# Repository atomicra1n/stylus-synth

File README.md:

# Stylus Synthesizer

A small synthesizer played with a stylus or a probe (such as a multimeter one). It has 20 copper pads on the PCB acting as a keyboard, a speaker and a headphone jack. Controlled by an RP2040-Zero featuring an analog vactrol circuit.

## Features

- 20 note keyboard (note C to G) from exposed copper pads, playable with a conductive stylus
- Notes fade out naturally when the stylus is lifted (thanks to the Vactrol circuit, LED + photoresistor)
- Volume and decay knobs
- Octave button and waveform button (supports square wave, saw wave and triangle wave)
- Speaker and a headphone jack that automatically turns the speaker off when headphones are plugged in
- Can also act as a USB MIDI controller
- Fully through-hole, easy to solder

## Motivation

Week 3 of Hack Club's Half Life was all about music. I remembered an interesting musical instrument from the 60s, which had small metal pads that would play notes when touched with a stylus (the Stylophone), so I decided to make my own smaller version. I also added a small vactrol circuit to make it sound more natural instead of notes cutting off.

## Functionality

- The keyboard has a chain of 21 1 kiloohm resistors between ground and 3.3 volts. Each pad is between two resistors, so it has a different voltage than the rest. The stylus goes into an ADC pin of the RP2040, so it can easily tell all 20 pads apart with just one pin. 
- The RP2040 produces sound as a fast PWM on the GP0 pin, so there are two low-pass filters (1 kiloohm resistor + 10 nanoFarad capacitor each) that smooth it into a waveform
- The vactrol circuit is simply a green LED shining on a photoresistor. They are sealed together with black heat-shrink. Together they make a filter that opens when the LED is on, and when the stylus lifts, the LED fades and the photoresistor slowly recovers in the dark. This means the note slowly gets quieter and more dull. If it doesn't work right, there is a jumper to bypass the vactrol circuit. 
- A 10 microFarad capacitor removes 1.65V DC from the PWM and two 100 kiloohm resistors make the signal smaller for the amplifier. There is a 10 kiloohm potentiometer for volume.
- The LM386 amp increases the signal 20 times and runs off 5V from the USB. 
- The headphone jack has a switch inside. Because the speaker goes through said switch, it turns off when the headphones plug in.

## How it was made

Everything was designed in KiCad. As I couldn't check my work gradually, I ran simulations in [Falstad](https://www.falstad.com/circuit/) to check values for the PWM and vactrol. Some issues that arised:

- The RP2040-Zero had no footprint, so I had to make my own, which was a bit tricky due to spacing between pins.
- The headphone jack I originally found on GM Electronic had no datasheet so I had no clue what the pinout was. I needed to switch to the ST-214C which did have one. 
- The datasheet I found for the potentiometers had a very blurry drawing which was hard to understand, so I had to make it out with quite the difficulty. I figured out the potentiometers seemingly mount sideways, meaning the knobs stick out the back edge. I also needed to watch the pin order, otherwise the knobs would turn the wrong way.
- I originally planned to add resistors in series with the headphone jack to make the headphones a bit quieter, but figured out that the resistors would also end up in the speaker path and make it way too quiet. So I made it that the volume knob controls both.
- I originally routed the amp input too long around the board which would introduce a lot of noise (the amp boosts all signal 20 times).

## Tech stack

- KiCad for the schematic and PCB
- Falstad for simulating the PWM and vactrol paths
- CircuitPython and synthio library for the firmware
- JLCPCB for board manufacturing, GM Electronic for components

## Repo layout

- pcb/ contains all the KiCad work (PCB, schematic, symbols, footprints...)
- pcb/gerbers contains the gerber and drill files
- firmware/ contains the CircuitPython firmware
- images/ contains renders, schematic, PCB layout and Falstad simulations
- BOM.csv contains the bill of materials

## Bill of materials

| Part | Qty | Source | Unit | Total |
|---|---|---|---|---|
| [CREATALL RP2040-Zero](https://www.gme.cz/v/1518920/creatall-rp2040-zero-vyvojovy-modul-dual-core-cortex-m0-2-mb-flash) | 1 | GM Electronic | $5.50 | $5.50 |
| [LM386N-1 amplifier](https://www.gme.cz/v/1487657/texas-instruments-lm386n-1-nopb-zesilovac) | 1 | GM Electronic | $1.40 | $1.40 |
| [DIL08PZ Socket](https://www.gme.cz/v/1501853/kls-dil08pz-patice) | 1 | GM Electronic | $0.40 | $0.40 |
| [Speaker (PSR-29N08S)](https://www.gme.cz/v/1498665/hitpoint-psr-29n08s-yhq-reproduktor) | 1 | GM Electronic | $0.85 | $0.85 |
| [Potentiometer (PC1621NBK010)](https://www.gme.cz/v/1494558/pc1621nbk010-potenciometr) | 2 | GM Electronic | $1.00 | $2.00 |
| [KN32 knob](https://www.gme.cz/v/1500373/kn32-knoflik-plastovy-prumer-266mm-osa-6mm-cerny) | 2 | GM Electronic | $0.70 | $1.40 |
| [ST-214C 3.5mm jack](https://www.gme.cz/v/1501907/st-214c-jack-35-stereo) | 1 | GM Electronic | $0.55 | $0.55 |
| [TS6601 button](https://www.gme.cz/v/1497943/kls-ts6601-43-180-mikrospinac) | 2 | GM Electronic | $0.11 | $0.22 |
| [S140C 1x40 pin header](https://www.gme.cz/v/1514383/s140c-bila-kolikova-lista-1x40pin-roztec-254mm) | 1 | GM Electronic | $0.40 | $0.40 |
| [2 layer 100x100 mm PCB (5 pieces)](https://jlcpcb.com/) | 1 | JLCPCB | $4.00 | $4.00 |
| [Black heat-shrink tubing CHS21-6.4](https://www.gme.cz/v/1519087/c-tie-chs21-64-smrstovaci-buzirka) | 1 | GM Electronic | $0.55 | $0.55 |
| [Resistor 1 kiloohm 1% 0207](https://www.gme.cz/v/1486228/gym-cym-rm-1k-06w-1-0207-metalizovany-rezistor) | 23 | GM Electronic | $0.09 | $2.07 |
| [Resistor 1 Megaohm 1% 0207](https://www.gme.cz/v/1486816/gym-cym-rm-1m-06w-1-0207-metalizovany-rezistor) | 10 | GM Electronic | $0.09 | $0.90 |
| [Resistor 100 kiloohm 1% 0207](https://www.gme.cz/v/1494147/gym-cym-rm-100k-06w-1-0207-metalizovany-rezistor) | 10 | GM Electronic | $0.09 | $0.90 |
| [Resistor 10 ohm 1% 0207](https://www.gme.cz/v/1494152/gym-cym-rm-10r-06w-1-0207-metalizovany-rezistor) | 10 | GM Electronic | $0.09 | $0.90 |
| [Resistor 330 ohm 1% 0207](https://www.gme.cz/v/1494116/gym-cym-rm-330r-06w-1-0207-metalizovany-rezistor) | 10 | GM Electronic | $0.09 | $0.90 |
| [Capacitor 220 microFarad 25V](https://www.gme.cz/v/1484171/jamicon-ce-220u-25vit-jam-tl-8x115-rm35-bulk-elektrolyticky-kondenzator) | 5 | GM Electronic | $0.04 | $0.20 |
| [Capacitor 10 microFarad 16V](https://www.gme.cz/v/1486104/hitano-ce-10u-16vit-hit-exr-5x11-rm2-bulk-elektrolyticky-kondenzator) | 6 | GM Electronic | $0.13 | $0.78 |
| [Capacitor 100 nanofarad](https://www.gme.cz/v/1489676/hitano-ck-100n-50v-x7r-rm508-10-keramicky-kondenzator) | 3 | GM Electronic | $0.25 | $0.75 |
| [Capacitor 10 nanofarad](https://www.gme.cz/v/1489673/hitano-ck-10n-50v-x7r-rm508-10-keramicky-kondenzator) | 5 | GM Electronic | $0.16 | $0.80 |
| [Capacitor 47 nanofarad](https://www.gme.cz/v/1486853/hitano-ck-47n-50v-x7r-rm508-10-keramicky-kondenzator) | 6 | GM Electronic | $0.13 | $0.78 |
| [Green LED 5mm L-53SGC](https://www.gme.cz/v/1491527/kingbright-l-53sgc-led-5mm-zelena) | 2 | GM Electronic | $0.15 | $0.30 |
| [Photoresistor LDR5516](https://www.gme.cz/v/1495847/ldr5516-fotorezistor) | 1 | GM Electronic | $0.33 | $0.33 |
| [Jumper cap](https://www.gme.cz/v/1499579/kls-jumper-black-zkratovaci-propojka) | 1 | GM Electronic | $0.10 | $0.10 |
| [Stranded wire 0.5mm2, pack of 5m](https://www.gme.cz/v/1512382/elektrokabel-cya-1x05-cerveny-h05v-k-izolovany-vodic-lanko) | 5 | GM Electronic | $0.15 | $0.75 |
| **Parts subtotal** | | | | **$27.73** |
| Shipping (estimate) | | | | $10.00 |
| **Total** | | | | **$37.73** |

The stylus is intentionally missing from the BOM. You can solder a multimeter probe or similar and it should work just fine.
The total is over the 30$ budget of tier 1 funding, I will cover the rest out of pocket. 

## Assembly

- Order the PCB from JLCPCB using the gerber files and order the components from any electronic store or GM Electronic if you're Czech.
- Begin with the resistors. Keep in mind all resistors in the resistor ladder (above the keyboard) are 1 kiloohm.
- Solder the ceramic capacitors, the DIP-8 socket, the buttons and pin headers.
- Solder the electrolytic capacitors (be very careful about the polarity, longer leg goes into +!)
- Solder the potentiometers and headphone jack on the back edge
- Solder the RP2040-Zero onto the pin headers. The USB should face the back edge.
- Put the LM386 amp in the socket matching the silkscreen.
- For the vactrol, try to bend the LED and photoresistor to make them face each other. Slide heat-shrink over both and shrink it to avoid any light getting in from outside.
- Solder two wires from the speaker to the SPEAKER pads.
- Solder the stylus wire (your multimeter probe or similar) to the STYLUS pad.
- Put the jumper on JP1 pin 2 and 3. This turns the vactrol on. If it sounds weird, you can move it to 1-2 and it will be bypassed.

## Firmware

- Download CircuitPython for the Waveshare RP2040-Zero [here](https://circuitpython.org/board/waveshare_rp2040_zero/).
- Hold the BOOT button on the RP2040, plug in the USB and drag the .uf2 file onto the drive that should show up in your system.
- When the CIRCUITPY drive shows up in your system, copy over firmware/code.py onto it.

## Controls

- Touch a pad with the stylus to play it or slide between pads to change notes.
- VOLUME knob controls the volume, DECAY controls notes fading.
- OCTAVE button switches between -1, 0 and 1 octave.
- WAVE button toggles square, saw or triangle wave.

## AI disclosure
LLMs (Claude Opus 5.5) was used to get feedback on the PCB schematic and routing, review parts of it and help with fixing bugs. It was also used for other tedious but simple tasks, such as adding the BOM to this README. AI was not used in writing the README, Journal or other parts of the project.

---
 
Built for [Hack Club Half Life](https://halflife.hackclub.com/) Week 3 (Music).

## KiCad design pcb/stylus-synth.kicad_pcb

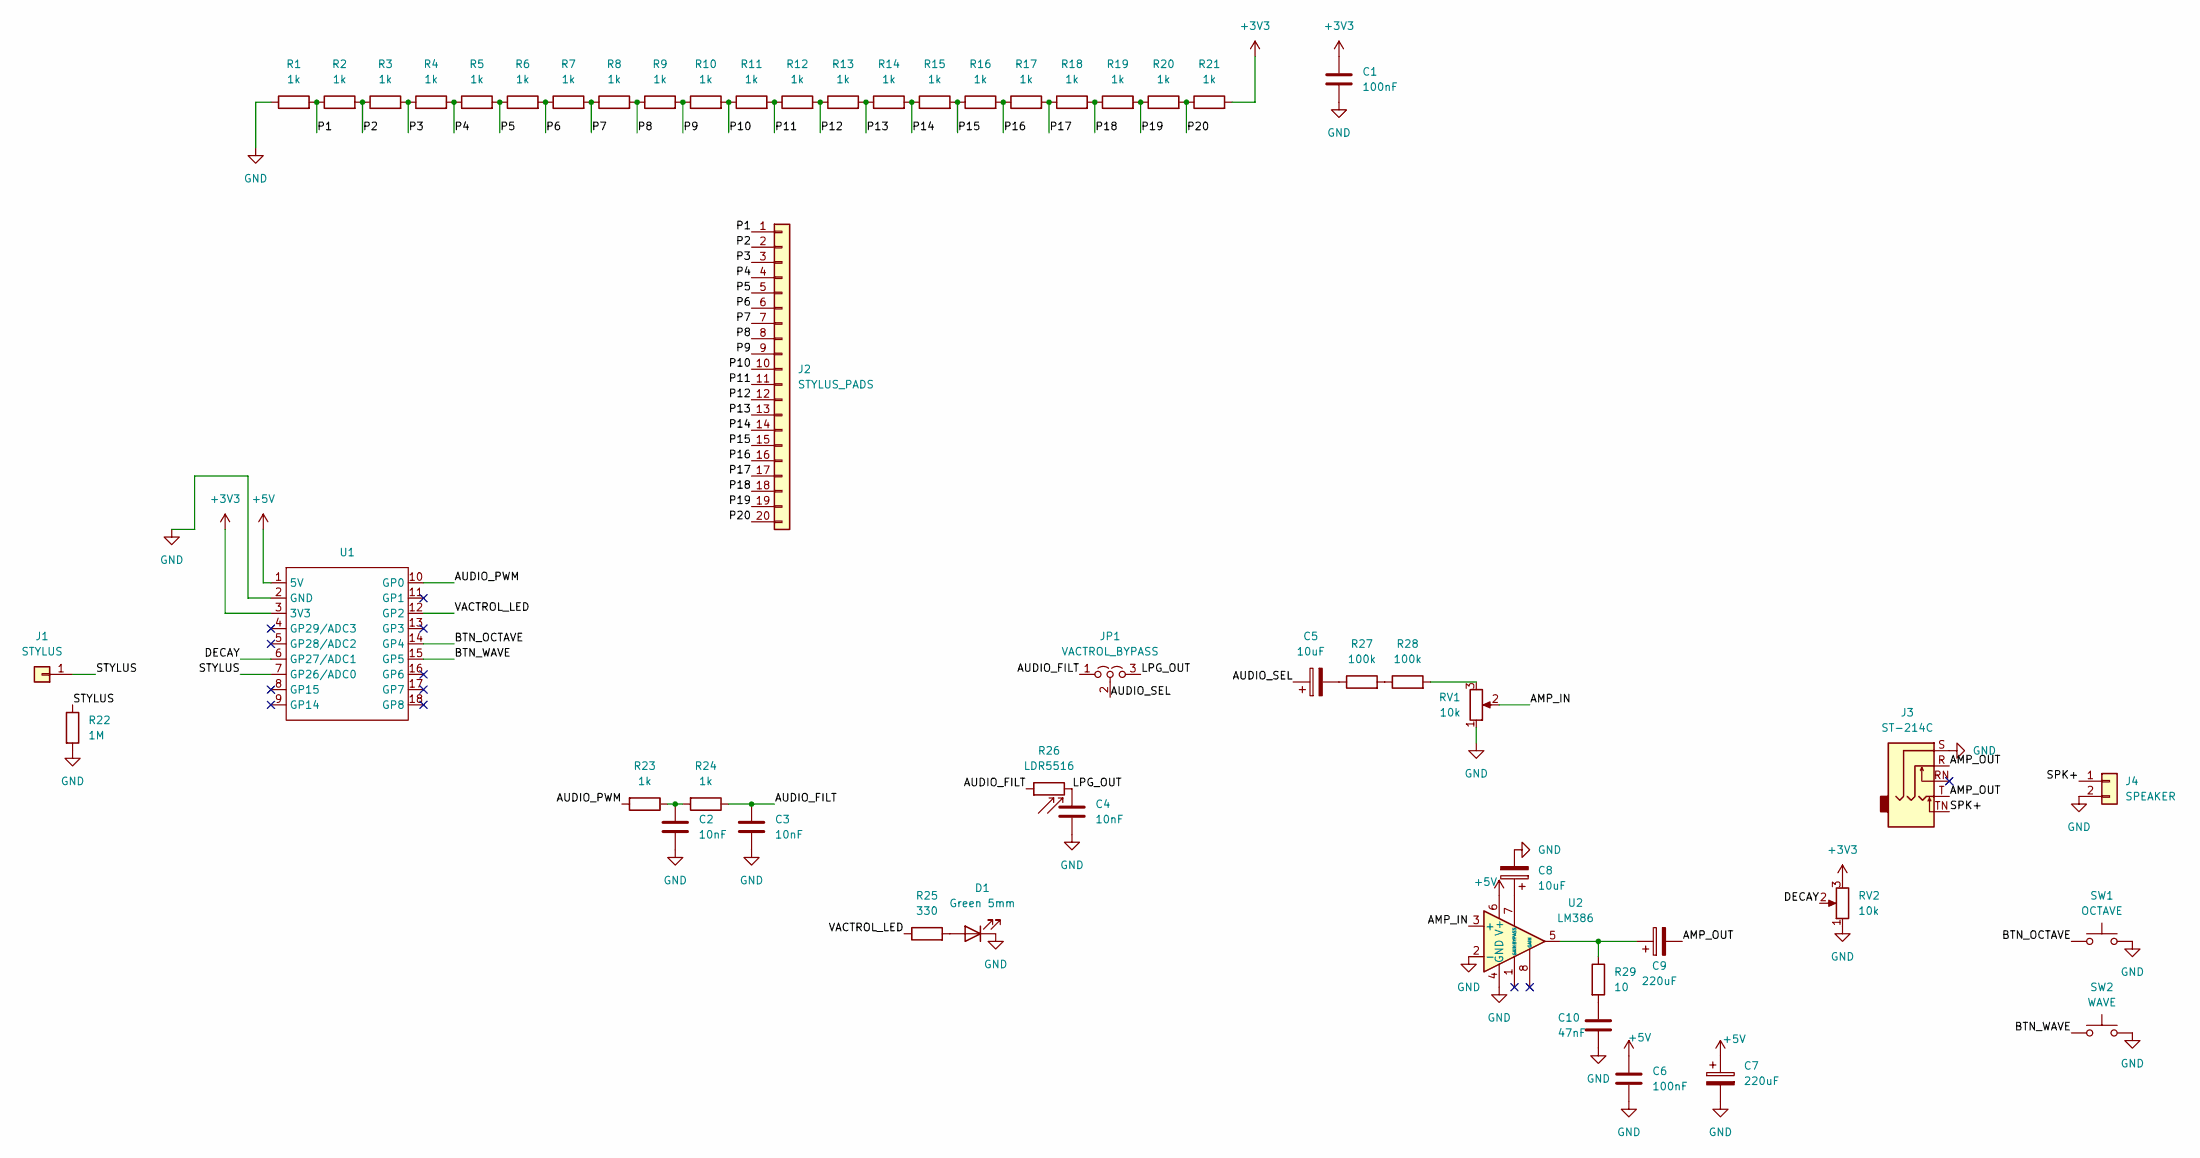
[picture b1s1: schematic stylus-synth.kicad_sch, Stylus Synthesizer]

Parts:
C1, C6: 100nF; C_Disc_D5.0mm_W2.5mm_P5.00mm
C2, C3, C4: 10nF; C_Disc_D5.0mm_W2.5mm_P5.00mm
C5, C8: 10uF; CP_Radial_D5.0mm_P2.00mm
C7, C9: 220uF; CP_Radial_D8.0mm_P3.50mm
C10: 47nF; C_Disc_D5.0mm_W2.5mm_P5.00mm
D1: Green 5mm; LED_D5.0mm
J1: STYLUS; SolderWire-0.5sqmm_1x01_D0.9mm_OD2.1mm_Relief
J2: STYLUS_PADS; StylusPads_20x4.5mm
J3: ST-214C; Jack_3.5mm_ST-214C
J4: SPEAKER; SolderWire-0.5sqmm_1x02_P4.6mm_D0.9mm_OD2.1mm_Relief
JP1: VACTROL_BYPASS; PinHeader_1x03_P2.54mm_Vertical
R1, R2, R3, R4, R5, R6, R7, R8, R9, R10, R11, R12, R13, R14, R15, R16, R17, R18, R19, R20, R21, R23, R24: 1k; R_Axial_DIN0207_L6.3mm_D2.5mm_P10.16mm_Horizontal
R22: 1M; R_Axial_DIN0207_L6.3mm_D2.5mm_P10.16mm_Horizontal
R25: 330; R_Axial_DIN0207_L6.3mm_D2.5mm_P10.16mm_Horizontal
R26: LDR5516; R_LDR_5.1x4.3mm_P3.4mm_Vertical
R27, R28: 100k; R_Axial_DIN0207_L6.3mm_D2.5mm_P10.16mm_Horizontal
R29: 10; R_Axial_DIN0207_L6.3mm_D2.5mm_P10.16mm_Horizontal
RV1, RV2: 10k; Pot_WH148_RightAngle
SW1: OCTAVE; SW_PUSH_6mm
SW2: WAVE; SW_PUSH_6mm
U1: RP2040-Zero
U2: LM386; DIP-8_W7.62mm_Socket

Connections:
+3V3: C1.1, R21.2, RV2.3, U1.3 (3V3)
+5V: C6.1, C7.1, U1.1 (5V), U2.6 (V+)
/AMP_IN: RV1.2, U2.3 (+)
/AMP_OUT: C9.2, J3.R, J3.T
/AUDIO_FILT: C3.1, JP1.1 (A), R24.1, R26.1
/AUDIO_PWM: R23.2, U1.10 (GP0)
/AUDIO_SEL: C5.1, JP1.2 (C)
/BTN_OCTAVE: SW1.1, U1.14 (GP4)
/BTN_WAVE: SW2.1, U1.15 (GP5)
/DECAY: RV2.2, U1.6 (GP27/ADC1)
/LPG_OUT: C4.1, JP1.3 (B), R26.2
/P1: J2.1, R1.2, R2.1
/P2: J2.2, R2.2, R3.1
/P3: J2.3, R3.2, R4.1
/P4: J2.4, R4.2, R5.1
/P5: J2.5, R5.2, R6.1
/P6: J2.6, R6.2, R7.1
/P7: J2.7, R7.2, R8.1
/P8: J2.8, R8.2, R9.1
/P9: J2.9, R9.2, R10.1
/P10: J2.10, R10.2, R11.1
/P11: J2.11, R11.2, R12.1
/P12: J2.12, R12.2, R13.1
/P13: J2.13, R13.2, R14.1
/P14: J2.14, R14.2, R15.1
/P15: J2.15, R15.2, R16.1
/P16: J2.16, R16.2, R17.1
/P17: J2.17, R17.2, R18.1
/P18: J2.18, R18.2, R19.1
/P19: J2.19, R19.2, R20.1
/P20: J2.20, R20.2, R21.1
/SPK+: J3.TN, J4.1
/STYLUS: J1.1 (Pin_1_1), R22.1, U1.7 (GP26/ADC0)
/VACTROL_LED: R25.1, U1.12 (GP2)
GND: C1.2, C2.2, C3.2, C4.2, C6.2, C7.2, C8.2, C10.1, D1.1 (K), J3.S, J4.2, R1.1, R22.2, RV1.1, RV2.1, SW1.2, SW2.2, U1.2 (GND), U2.2 (-), U2.4 (GND)
unnamed: C2.1, R23.1, R24.2
unnamed: C5.2, R27.1
unnamed: C9.1, R29.1, U2.5
unnamed: C10.2, R29.2
unnamed: D1.2 (A), R25.2
unnamed: R27.2, R28.1
unnamed: R28.2, RV1.3
unnamed: C8.1, U2.7 (BYPASS)

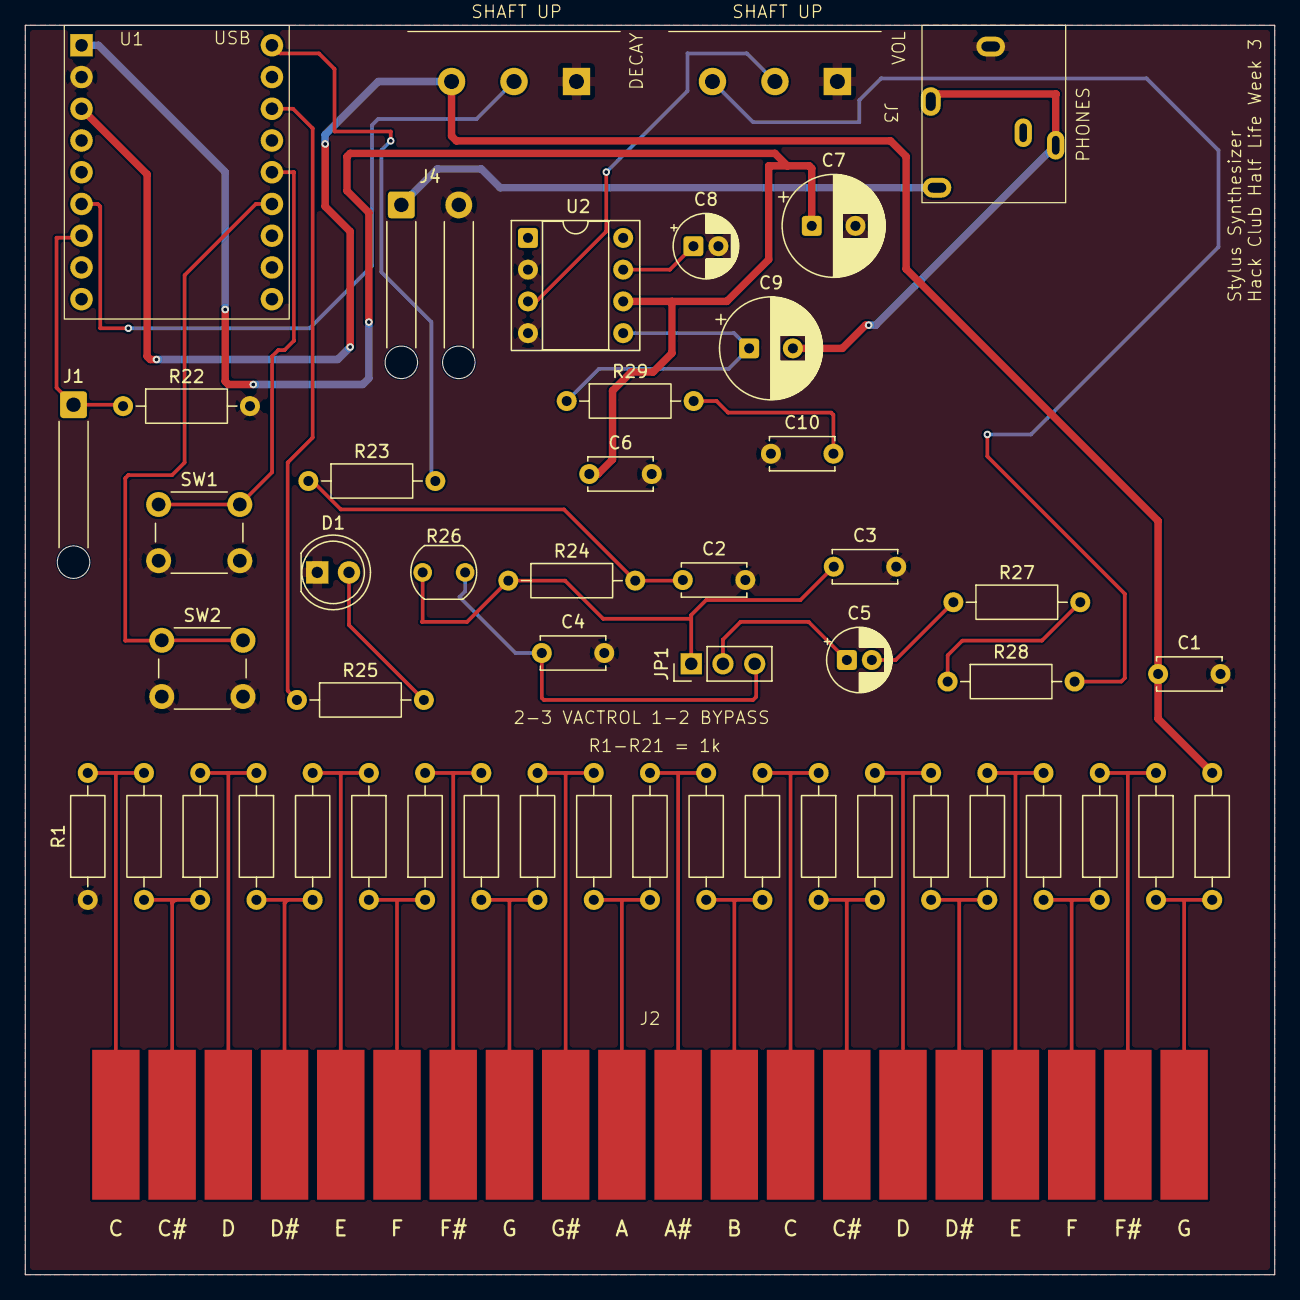
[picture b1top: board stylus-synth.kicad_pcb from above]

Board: 2 copper layers, 100.0 x 100.0 mm, 51 parts (0 on the bottom side), 43 nets.
